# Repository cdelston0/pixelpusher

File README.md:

# pixelpusher
Software for a USB to WS28xx LED pixel interface using the RP2350 / Pico 2

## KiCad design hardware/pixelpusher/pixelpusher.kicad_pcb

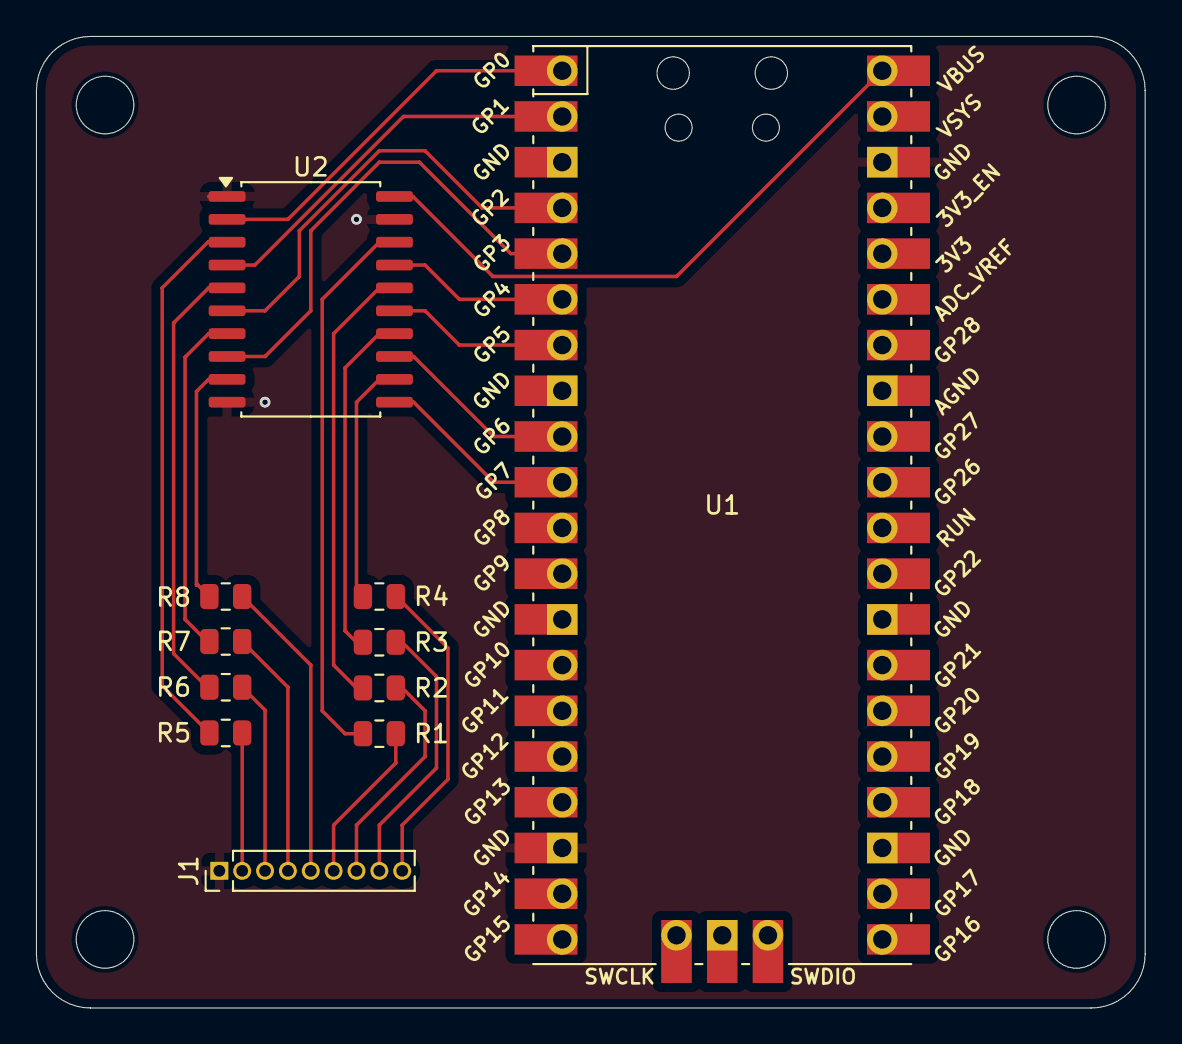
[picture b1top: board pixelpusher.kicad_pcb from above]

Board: 2 copper layers, 61.6 x 54.0 mm, 15 parts (0 on the bottom side), 26 nets.

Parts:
H1, H2, H3, H4: MountingHole; MountingHole_3.2mm_M3
J1: Conn_01x09_Pin; PinHeader_1x09_P1.27mm_Vertical
R1, R2, R3, R4, R5, R6, R7, R8: 560R; R_0805_2012Metric
U1: Pico; RPi_Pico_SMD_TH
U2: 74HCT244; SOIC-20W_7.5x12.8mm_P1.27mm

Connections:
GND: J1.1, U1.18 (GND), U1.38 (GND), U2.1 (1OE), U2.10 (GND), U2.19 (2OE)
unnamed: J1.2, R5.2
unnamed: J1.3, R6.2
unnamed: J1.4, R7.2
unnamed: J1.5, R8.2
unnamed: J1.6, R1.2
unnamed: J1.7, R2.2
unnamed: J1.8, R3.2
unnamed: J1.9, R4.2
unnamed: U1.1 (GPIO0), U2.2 (1A0)
unnamed: U1.2 (GPIO1), U2.4 (1A1)
unnamed: U1.4 (GPIO2), U2.6 (1A2)
unnamed: U1.5 (GPIO3), U2.8 (1A3)
unnamed: U1.6 (GPIO4), U2.17 (2A0)
unnamed: U1.7 (GPIO5), U2.15 (2A1)
unnamed: U1.9 (GPIO6), U2.13 (2A2)
unnamed: U1.10 (GPIO7), U2.11 (2A3)
unnamed: R1.1, U2.18 (1Y0)
unnamed: R2.1, U2.16 (1Y1)
unnamed: R3.1, U2.14 (1Y2)
unnamed: R4.1, U2.12 (1Y3)
unnamed: R5.1, U2.3 (2Y0)
unnamed: R6.1, U2.5 (2Y1)
unnamed: R7.1, U2.7 (2Y2)
unnamed: R8.1, U2.9 (2Y3)
VCC: U1.40 (VBUS), U2.20 (VCC)

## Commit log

2025-09-21 Initial commit for RP2350 USB pixelpusher
2025-09-27 Fix DMA and remove buffer size configuration
    - Whilst working on the python code and trying to maintain a level
    of compatibility with the PixelBlaze output expander, I realised
    that we don't really need the user to configure the size of the buffer
    ahead of time. They can just send us pixel data and as long as it fits
    inside the fixed-sized buffer, we can send it out. So I removed the
    storing and configuring of the channel output size.
2026-01-04 Add a (very basic) PCB for pixelpusher
    Created a level-shifter PCB for the Pi Pico 2 for use as dedicated
    pixelpusher hardware. Very bare-bones.
